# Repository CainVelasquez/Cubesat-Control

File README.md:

# Cubesat Controle

## Descrição
Desenvolvimento do sistema de controle de atitude

## Envolvidos
- Felipe
- Augusto
- William

## Organização das pastas

As pastas desse projeto devem ser organizadas conforme exemplo a seguir:

- Como : Toda documentação gerada e coletada que pode ser usada para compreenção e descrição do projeto

- Materiais : Todo formato de material desenvolvido no projeto, inclui softwares, esquemáticos, fotos, etc..

Árvore de arquivos :
```
└──  Materiais
├── Como
│   ├── Apresentações
│   ├── Artigos
│   │   └── Bibliografia
│   ├── Datasheets
│   ├── Estudos
│   ├── Manuais
│   └── Wiki
└──  Materiais
    ├── Arquivos
    │   └── Orçamentos
    ├── Códigos
    │   ├── Altera
    │   ├── Arduino
    │   ├── Atmel
    │   ├── C
    │   ├── Comsol
    │   ├── Labview
    │   ├── Matlab
    │   └── Xilinx
    ├── Fotos
    ├── Mecânica
    ├── PCB
    └── Referências
```

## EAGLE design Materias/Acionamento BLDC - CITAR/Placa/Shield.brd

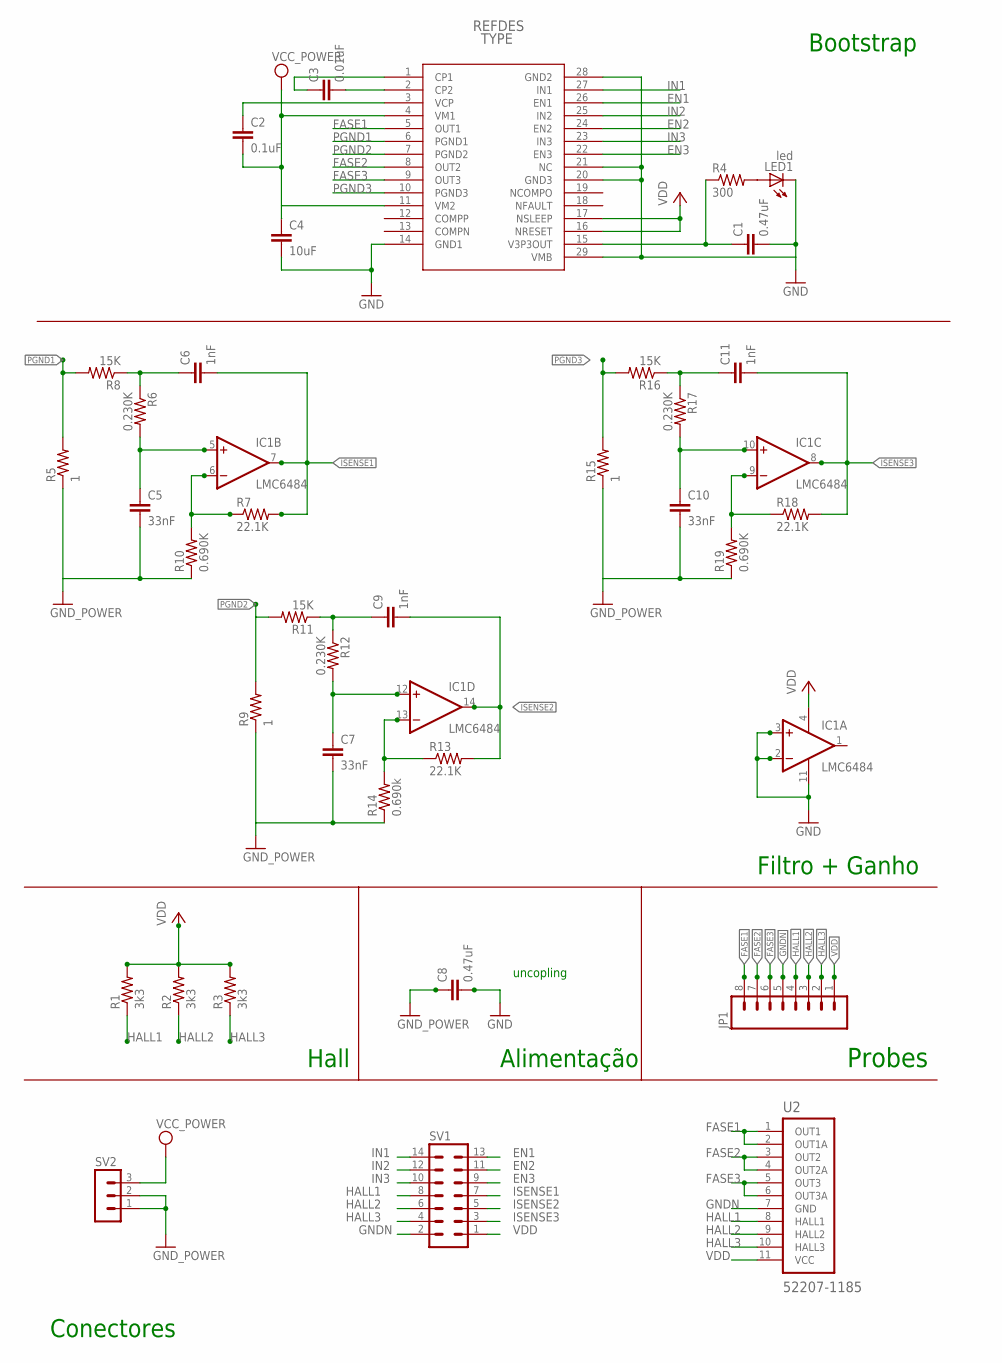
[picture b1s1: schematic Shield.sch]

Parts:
C1, C8: 0.47uF; C1206
C2: 0.1uF; C1206
C3: 0.01uF; C1206
C4: 10uF; C1206
C5, C7, C10: 33nF; C1206
C6, C9, C11: 1nF; C1206
IC1: LMC6484; SO14
JP1: M08; 1X08_ROUND
LED1: led; CHIPLED_1206
R1, R2, R3: 3k3; R1206
R4: 300; R1206
R5, R9, R15: 1; R2512
R6, R12, R17: 0.230K; R1206
R7, R13, R18: 22.1K; R1206
R8, R11, R16: 15K; R1206
R10, R19: 0.690K; R1206
R14: 0.690k; R1206
SV1: MA07-2
SV2: MA03-1
U1: DRV8811_PWP_28; PWP28_5P18X3P1
U2: 52207-1185; MOLEX_52207-1185

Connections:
EN1: SV1.13, U1.26 (EN1)
EN2: SV1.11, U1.24 (EN2)
EN3: SV1.9, U1.22 (EN3)
FASE1: JP1.8, U1.5 (OUT1), U2.1 (OUT1), U2.2 (OUT1A)
FASE2: JP1.7, U1.8 (OUT2), U2.3 (OUT2), U2.4 (OUT2A)
FASE3: JP1.6, U1.9 (OUT3), U2.5 (OUT3), U2.6 (OUT3A)
GND: C5.2, C7.2, C10.2, IC1.2 (-IN), IC1.3 (+IN), IC1.11 (V-), R5.1, R9.1, R10.1, R14.1, R15.1, R19.1
GNDN: C1.2, C4.2, C8.2, JP1.5, LED1.C, SV1.2, SV2.1, SV2.2, U1.14 (GND1), U1.20 (GND3), U1.21 (NC), U1.28 (GND2), U1.29 (VMB), U2.7 (GND)
GND_POWER: C8.1
HALL1: JP1.4, R1.1, SV1.8, U2.8 (HALL1)
HALL2: JP1.3, R2.1, SV1.6, U2.9 (HALL2)
HALL3: JP1.2, R3.1, SV1.4, U2.10 (HALL3)
IN1: SV1.14, U1.27 (IN1)
IN2: SV1.12, U1.25 (IN2)
IN3: SV1.10, U1.23 (IN3)
ISENSE1: C6.2, IC1.7 (OUT), R7.2, SV1.7
ISENSE2: C9.2, IC1.14 (OUT), R13.2, SV1.5
ISENSE3: C11.2, IC1.8 (OUT), R18.2, SV1.3
unnamed: C2.1, U1.3 (VCP)
unnamed: C5.1, IC1.5 (+IN), R6.2
unnamed: IC1.6 (-IN), R7.1, R10.2
unnamed: C6.1, R6.1, R8.1
unnamed: C9.1, R11.1, R12.1
unnamed: C7.1, IC1.12 (+IN), R12.2
unnamed: IC1.13 (-IN), R13.1, R14.2
unnamed: C11.1, R16.1, R17.1
unnamed: C10.1, IC1.10 (+IN), R17.2
unnamed: LED1.A, R4.2
unnamed: C1.1, R4.1, U1.15 (V3P3OUT)
unnamed: IC1.9 (-IN), R18.1, R19.2
unnamed: C3.2, U1.2 (CP2)
unnamed: C3.1, U1.1 (CP1)
PGND1: R5.2, R8.2, U1.6 (PGND1)
PGND2: R9.2, R11.2, U1.7 (PGND2)
PGND3: R15.2, R16.2, U1.10 (PGND3)
VCC_POWER: C2.2, C4.1, SV2.3, U1.4 (VM1), U1.11 (VM2)
VDD: IC1.4 (V+), JP1.1, R1.2, R2.2, R3.2, SV1.1, U1.16 (NRESET), U1.17 (NSLEEP), U2.11 (VCC)

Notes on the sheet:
uncopling
Bootstrap
Filtro + Ganho
Alimentação
Conectores
Hall
Probes

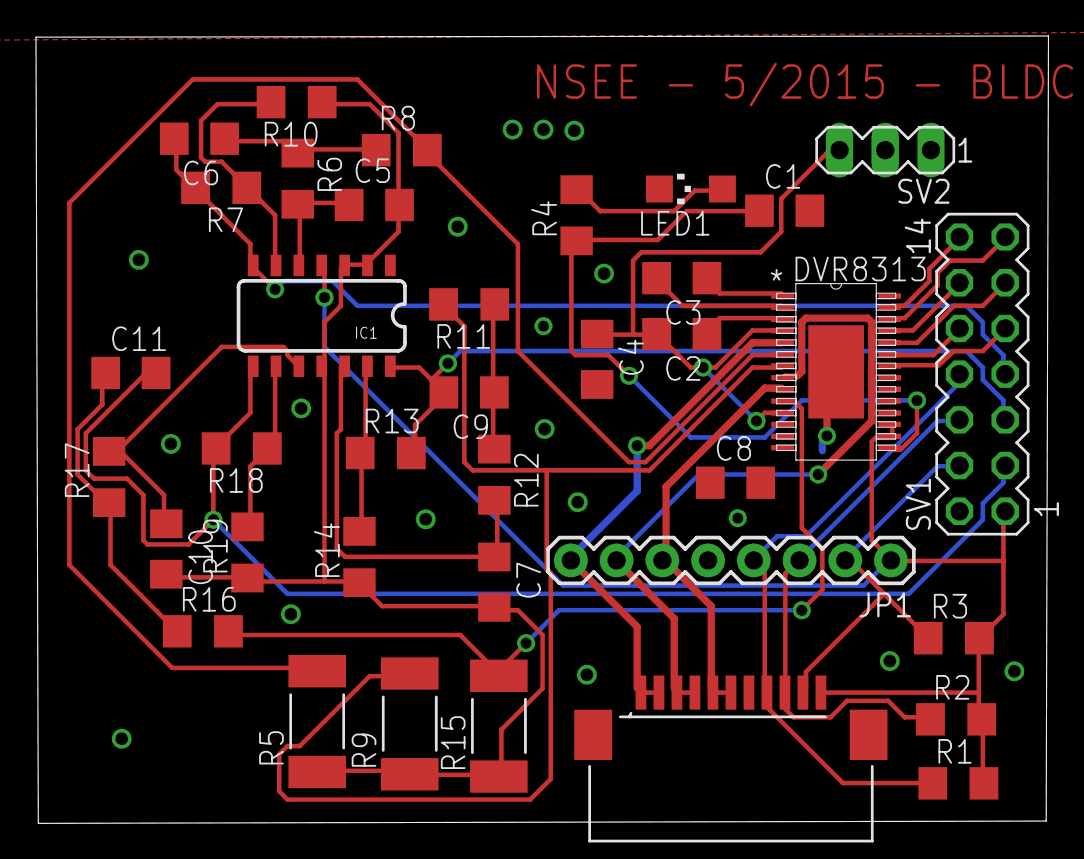
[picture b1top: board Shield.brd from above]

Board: 2 copper layers, 56.2 x 43.7 mm, 37 parts (0 on the bottom side), 36 nets.

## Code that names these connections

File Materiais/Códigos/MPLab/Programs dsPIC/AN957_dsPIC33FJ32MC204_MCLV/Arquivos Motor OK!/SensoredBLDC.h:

//---------------------------------------------------------------------
//
//							 Software License Agreement
//
// The software supplied herewith by Microchip Technology Incorporated 
// (the Company) for its PICmicro® Microcontroller is intended and 
// supplied to you, the Companys customer, for use solely and 
// exclusively on Microchip PICmicro Microcontroller products. The 
// software is owned by the Company and/or its supplier, and is 
// protected under applicable copyright laws. All rights are reserved. 
//  Any use in violation of the foregoing restrictions may subject the 
// user to criminal sanctions under applicable laws, as well as to 
// civil liability for the breach of the terms and conditions of this 
// license.
//
// THIS SOFTWARE IS PROVIDED IN AN AS IS CONDITION. NO WARRANTIES, 
// WHETHER EXPRESS, IMPLIED OR STATUTORY, INCLUDING, BUT NOT LIMITED 
// TO, IMPLIED WARRANTIES OF MERCHANTABILITY AND FITNESS FOR A 
// PARTICULAR PURPOSE APPLY TO THIS SOFTWARE. THE COMPANY SHALL NOT, 
// IN ANY CIRCUMSTANCES, BE LIABLE FOR SPECIAL, INCIDENTAL OR 
// CONSEQUENTIAL DAMAGES, FOR ANY REASON WHATSOEVER.
//
//---------------------------------------------------------------------
//	File:		SensoredBLDC.h
//
//						
// 
// The following files should be included in the MPLAB project:
//
//		SensoredBLDC.c		-- Main source code file
//		Interrupts.c
//		Init.c
//		SensoredBLDC.h		-- Header file
//		p33FJ32MC204.gld	-- Linker script file
//				
//
//---------------------------------------------------------------------- 

/*
Using the Fosc = Fin * (M/(N1*N2))
Where:
Fin 	= 8Mhz
M 	= PLLFBD[PLLDIV<8:0>] 	= 0x26	then M = 40  (PLLDIV + 2)
N1	= CLKDIV[PLLPRE<4:0>] 	= 0x0 	then N1 = 2  (PLLPRE + 2)
N2	= CLKDIV[PLLPOST<1:0>]	= 0x3	then N2 = 8 

CLKDIV = 0x30C0
PLLFBD = 0x0026

?	Fosc =	(8M * (40 / (8 * 2)))  = 20Mhz
?	Fcy  =	20M/2 = 10MIP
*/

//#define CLOSEDLOOP
#define FOSC  120000000			// xtal = 10.0Mhz, 120.0Mhz after PLL
#define FCY  FOSC/2				
#define MILLISEC FCY/60000		// 1 mSec delay constant
#define FPWM 39000

#define POLEPAIRS		4		// number of pole pairs
#define HALL_INDEX_R	6		// Hall sensor position index
#define HALL_INDEX_F	5		// Hall sensor position index

#define LED     LATAbits.LATA1
#define	PLED	PORTAbits.RA1
#define EN1     LATBbits.LATB15
#define EN2     LATBbits.LATB13
#define EN3     LATBbits.LATB11
#define RESET8313N LATAbits.LATA4
#define SLEEP8313N LATBbits.LATB5
#define FAULT8313N PORTBbits.RB6
#define PRESET8313N PORTAbits.RA4
#define PSLEEP8313N PORTBbits.RB5
#define HALL1	PORTBbits.RB0
#define HALL2	PORTBbits.RB1
#define HALL3	PORTBbits.RB7

#define T1PR1 ((FCY/1000)/8)

/* Based on using the internal Fcy and Timer 3 prescaler of 256
 * Fcy/256 = 10M/256 = 39062.5 ticks/sec
 * or, 2343750 ticks = 1RPM
 * => RPM would be 2343750/T3ticks
 */
//#define SPEEDMULT	2343750
//define OFFSET 8
//#define POTMULT 4				// pot to speed ratio

//#define Kps	50					// Kp and Ks terms need to be adjusted
//#define Kis	1					// as per the motor and load 

struct MotorFlags
{
unsigned RunMotor 	:1;
unsigned Direction	:1;
unsigned Sentido	:1;
unsigned unused		:13;
};
extern struct MotorFlags Flags;

extern int setpoint;
extern int velocidade;
extern int velocidade1;
extern unsigned int HallValue;
extern unsigned int timer3value;
extern unsigned int timer3avg;
extern unsigned int timer1value;
extern unsigned int timer1avg;
extern unsigned int polecount;

extern unsigned int StateTableFwd[];
extern unsigned int StateTableRev[];

extern unsigned char RAMBuffer[256];	//RAM area which will work as EEPROM for Master I2C device

struct FlagType
{
	unsigned char AddrFlag:1;
	unsigned char DataFlag:1;
};
extern struct FlagType Flag;

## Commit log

2015-05-06 versao nova da placa de acionamento com outro ampop
2015-05-06 removido lixo
2015-05-07 adicionado BOM e PCB lucas
2015-05-28 V1
    Primeiro upload das placas de controle dos motores
2015-05-28 Revert "V1"
    This reverts commit c67eeae46dcaf9f8b5f9b61616df49a076ec1c0c.
2015-05-29 Datasheet
2015-05-29 Remoção de pasta de exemplo
2015-05-29 Materiais
2015-05-29 Apresentações
2015-05-29 Referências
2015-05-29 Correção do local onde fica o Datasheet
2015-05-29 Imagens
2015-05-29 Correção de onde ficam os arquivos de materiais
2015-05-31 Modelo Solid
2015-05-31 Outras Referências
2015-05-31 Modelo do Motor
2015-06-02 Imagem Roda de Reação
2015-06-04 Folhas de fabricação
2015-06-06 Correção do modelo usado
2015-06-07 CubeSat Control
2015-06-08 Placas PCB
    Atualização das placas PCB no SolidWorks para futura conversão para o
    Eagle
2015-07-01 Orçamentos
2015-07-06 Atualizações mecânicas
2015-07-07 Monografia
2015-07-07 Modelo em SolidWorks
2015-07-10 correção do modelo do suporte
2015-07-13 Correção do nome da pasta
2015-07-13 Arquivos para Impressão 3D
2015-07-15 Atualização Fabricação
2015-08-06 Atualização SolidWorks
2015-08-06 Atualização Monografia
2015-08-15 Atualização Modelos SolidWorks
2015-08-27 Atualização Apresentações
2015-08-27 Atualização Imagens de Referências
2015-08-27 Atualização Materiais
2015-08-27 Remoção Imagens de Materiais
2015-11-02 Atualizações Gerais P1
2015-11-02 Atualizações Gerais P2
2015-11-02 Atualizações Gerais P3
2015-11-02 Atualizações Gerais P4
2015-12-17 Atualização Geral Final

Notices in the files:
parts and their libraries:
SparkFun-Connectors: Licensing: Creative Commons ShareAlike 4.0 International - https://creativecommons.org/licenses/by-sa/4.0
